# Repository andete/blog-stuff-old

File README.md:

blog-stuff
==========

Miscelaneous code, schematics, ... from blog posts.

Unless otherwise stated in the file, all code is GPLv3+ licensed
and all schematic and board files are CC0 licensed.

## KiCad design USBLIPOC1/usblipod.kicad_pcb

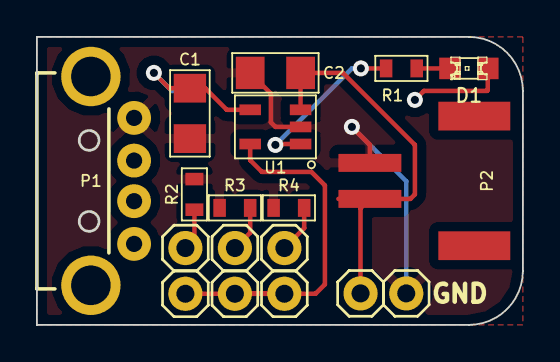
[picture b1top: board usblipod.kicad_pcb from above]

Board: 2 copper layers, 27.0 x 15.9 mm, 14 parts (0 on the bottom side), 9 nets.

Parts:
C1, C2: 4.7uF; 1206
D1: Red; LED-0805
P1: USB-A-H
P2: JST-PH-2; PIN 1X2_JST_PH_SMT
P3, P4, P5, P6: CONN_2; PIN 1X2_S
R1: 1k; 0603_S
R2, R3, R4: R; 0603_S
U1: MCP73832; SOT-23-5

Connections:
/P1: P4.2, R2.1
/P2: P5.2, R3.1
/P3: P6.2, R4.1
/STAT: R1.1, U1.1
/STATLED: D1.2, R1.2
/VBAT: C2.1, P2.1, P3.1, U1.3
GND: C1.2, C2.2, P1.GND, P2.2, P3.2, R2.2, R3.2, R4.2, U1.2
unnamed: P4.1, P5.1, P6.1, U1.5
VCC: C1.1, D1.1, P1.VBUS, U1.4

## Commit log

2013-05-02 initial import HPLEDRF
2013-05-02 add readme
2013-05-02 cleanup (part1)
2013-05-02 cleanup (part2)
2013-05-02 cleanup (part3)
2013-05-02 cleanup (part4)
2013-05-02 cleanup (part5)
2013-05-02 cleanup (part6)
2013-05-02 swap on/off relay; send ack after using msg data or data is gone
2013-05-02 testing code; cleanup
2013-05-04 lower LED pwm frequency; add fan on/off pin; disable fan code; add NO_BEEP setting
2013-05-05 more fan control steps; more temperature measurement steps
2013-05-05 fan speed interpolated on temperature
2013-05-09 fan on/off handling code (done with high-side P-channel mosfet switching)
2013-05-09 log pulse fail counting
2013-05-21 add code for http://joost.damad.be/2012/10/software-serial-possible-alternative.html
2013-05-28 add NullSerial.h
2013-05-31 add BufferSerial
2013-05-31 update URL
2013-07-04 add initial relay_pwm sketch
2013-07-04 temp_fan sketch; initial layout
2013-07-04 basic functionality for temp_fan sketch
2013-07-05 cleanup temp_fan sketch
2013-07-05 externalize settings
2013-07-05 relay_pwm sketch mostly works
2013-07-05 log enable/disable of relay/LED
2013-07-05 tune defaults: fan_pwm:64; idle:30lc
2013-07-22 wrap up HPLEDRF2
2013-07-23 add schematic and board
2013-08-09 add avrdude.conf with atxmega16e5 definition
2013-08-09 add atxmega32e5 device signature
2013-08-10 make clear that this is avrdude 6 config file
2013-08-10 fix atxmega16e5 and atxmega32e5 memory layout info
2013-08-10 add avrdude5.conf (not working!)
2013-08-10 use C++ isof C; use atxmega32e5; remove avrdude5.conf; full working example :)
2013-08-10 add README.md; add for_avr-libc stuff; cosmetic fixes
2013-08-11 add links to README.md
2013-08-13 add BT111 stuff
2013-09-13 add images of bt111 breakout schematic
2013-09-13 explain licensing
2013-09-13 add CC0 license
2013-09-13 add pictures
2013-09-13 add kicad schematic and board
2013-09-13 add pdf of schematic
2013-12-14 add stm32f105 sample blink code

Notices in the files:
USBLIPOC1/usblipod.kicad_pcb:
License: CC0
(c) 2013 joost@damad.be
